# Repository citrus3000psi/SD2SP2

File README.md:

# SD2SP2

This PCB allows a MicroSD card to adapted into the serial port2 of the gamecube.

The PCB must be ordered in 1.2mm thickness. Surface finish must be ENIG at minimum.  I recommened https://jlcpcb.com for PCB production

BOM:  

C1: 0805 22u Capactior (10V Min) - DigiKey Part# 	1276-6780-1-ND  

J1: MicroSD Slot - DigiKey Part# WM6825CT-ND  

Unassembled kits will be available for purchase at my webstore soon: https://shop.dansprojects.com

Special thanks to:  
 * MockyLock for the idea  
 * Extrems & emu_kidid for doing the real work needed to make this possible

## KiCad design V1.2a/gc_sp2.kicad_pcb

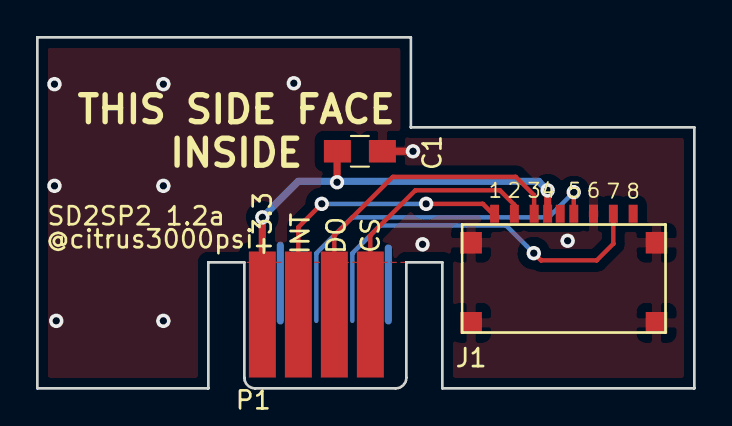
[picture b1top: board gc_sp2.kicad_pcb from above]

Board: 2 copper layers, 36.5 x 19.5 mm, 3 parts (0 on the bottom side), 7 nets.

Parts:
C1: .1; C_0805_HandSoldering
J1: Micro_SD_Card; 1050270001
P1: SerialPort; SP2_FootPrint

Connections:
/+3.3: C1.1, J1.4, P1.1
/CLK: J1.5, P1.4
/CS: J1.2, P1.7
/DI: J1.3, P1.5
/DO: J1.7, P1.6
/INT: J1.1, P1.3
GND: C1.2, J1.6, J1.9, P1.2, P1.8

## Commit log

2019-05-17 Added Design Files
2019-05-17 Added Images
2019-05-17 Updated Design
2019-05-17 Added Gerber
2019-10-14 README cleanup
2019-11-06 1.2a moved cap to sd side for easier PCBA
